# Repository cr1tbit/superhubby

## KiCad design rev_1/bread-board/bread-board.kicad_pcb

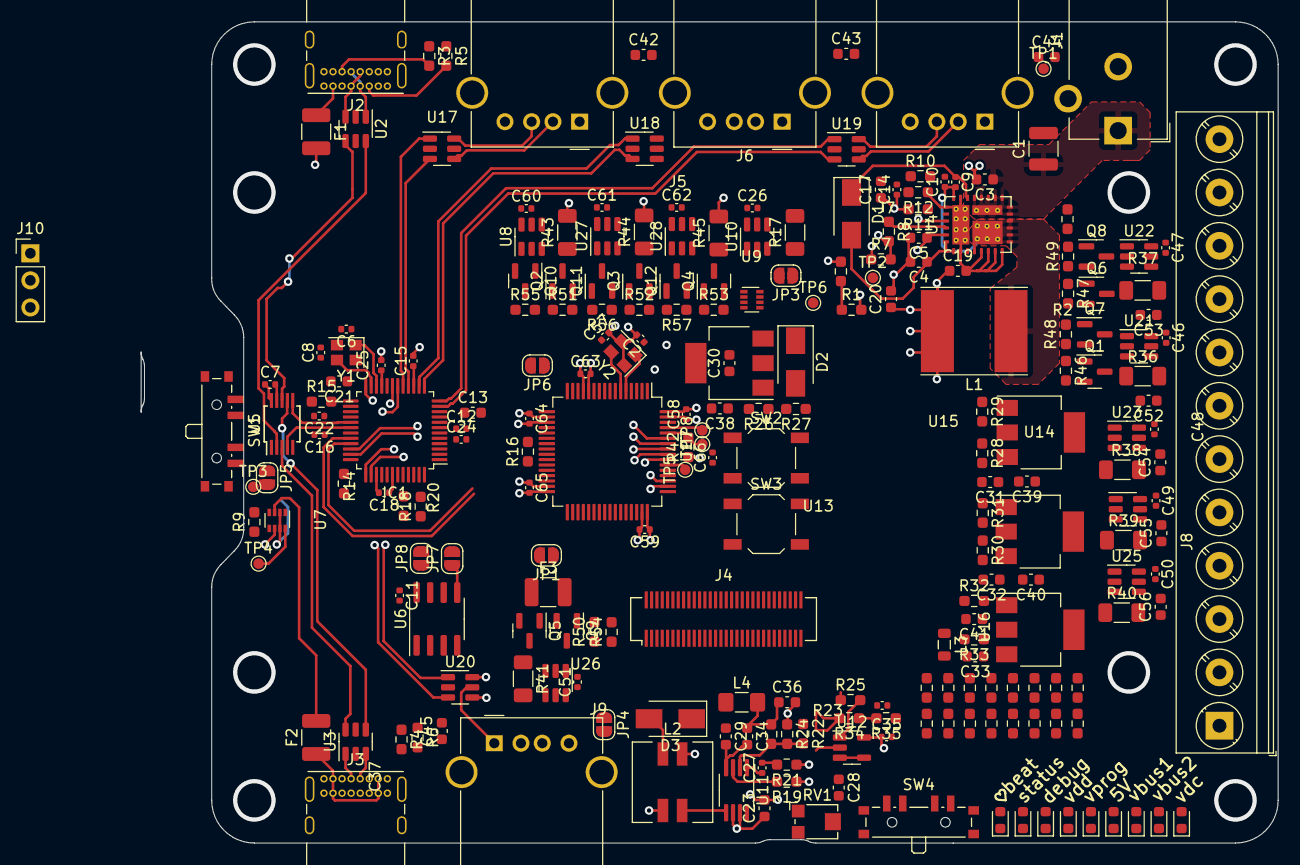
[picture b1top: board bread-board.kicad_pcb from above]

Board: 4 copper layers, 106.6 x 77.0 mm, 232 parts (1 on the bottom side), 174 nets.

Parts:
C1: C; C_1210_3225Metric
C2, C6, C8, C57: 20p; C_0402_1005Metric
C3, C4, C5, C13, C17, C21, C23, C29, C30, C31, C32, C33, C34, C38, C39, C40, C41, C42, C43, C44, C45, C52, C54, C55, C56: 10u; C_0603_1608Metric
C7, C9, C10, C11, C12, C14, C15, C16, C18, C22, C24, C25, C26, C27, C35, C37, C46, C47, C48, C49, C50, C51, C58, C59, C60, C61, C62, C63, C64, C65, C66: 100n; C_0402_1005Metric
C19, C20: 22u; C_0603_1608Metric
C28: 2.2u; C_0603_1608Metric
C36: 47u; C_0603_1608Metric
C53: 10u/16V; C_0603_1608Metric
D1, D2, D3: D_Schottky; D_SMA
D4, D5, D6, D7, D8, D9, D10, D11, D12: LED; LED_0603_1608Metric
F1, F2, F3: 1A; R_1210_3225Metric_Pad1.30x2.65mm_HandSolder
IC1: FE2.1; LQFP-48_7x7mm_P0.5mm
J1: Barrel_Jack_Switch; BarrelJack_CUI_PJ-102AH_Horizontal
J2, J3: USB_C_Receptacle_USB2.0; USB_C_Receptacle_GCT_USB4085
J4: Conn_02x30_Top_Bottom; Hirose_DF12_DF12E3.0-60DP-0.5V_2x30_P0.50mm_Vertical
J5: USB2; USB_A_Molex_67643_Horizontal
J6: USB3; USB_A_Molex_67643_Horizontal
J7: USB4; USB_A_Molex_67643_Horizontal
J8: Screw_Terminal_01x12; TerminalBlock_Phoenix_PT-1,5-12-5.0-H_1x12_P5.00mm_Horizont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
J9: USB1; USB_A_Molex_67643_Horizontal
J10: Conn_01x03; PinHeader_1x03_P2.54mm_Vertical
JP1: FUSE_BYP; SolderJumper-2_P1.3mm_Open_RoundedPad1.0x1.5mm
JP2: USB1_PWR_BYP; SolderJumper-2_P1.3mm_Open_RoundedPad1.0x1.5mm
JP3: 5V_BYP; SolderJumper-2_P1.3mm_Open_RoundedPad1.0x1.5mm
JP4: TEST_POT_ENA; SolderJumper-2_P1.3mm_Open_RoundedPad1.0x1.5mm
JP5: MCU_USB_MUX_ENA; SolderJumper-2_P1.3mm_Open_RoundedPad1.0x1.5mm
JP6, JP7, JP8: X; SolderJumper-2_P1.3mm_Open_RoundedPad1.0x1.5mm
L1: 2.2u; L_Taiyo-Yuden_NR-80xx_HandSoldering
L2: L_Iron_Coupled; L_Wuerth_WE-DD-Typ-M-Typ-S
L3: L_Ferrite; L_0805_2012Metric
L4: L_Iron; L_1206_3216Metric_Pad1.42x1.75mm_HandSolder
Q1, Q2, Q3, Q4, Q5, Q6: AO3401A; SOT-23
Q7, Q8, Q9, Q10, Q11, Q12: BC847; SOT-23
R1: 470k; R_0603_1608Metric_Pad0.98x0.95mm_HandSolder
R2, R7, R8, R9, R10, R11, R12, R14, R15, R16, R19, R20, R21, R26, R27, R28, R29, R30, R31, R32, R33, R34, R35, R72, R73: 100k; R_0603_1608Metric_Pad0.98x0.95mm_HandSolder
R3, R4, R5, R6: 5.1k; R_0603_1608Metric_Pad0.98x0.95mm_HandSolder
R13, R42, R46, R47, R50, R51, R52, R53: 10k; R_0603_1608Metric_Pad0.98x0.95mm_HandSolder
R17: 0.5R; R_1206_3216Metric_Pad1.30x1.75mm_HandSolder
R18: 0R; R_0603_1608Metric_Pad0.98x0.95mm_HandSolder
R22, R24, R58, R60, R61, R62, R63, R64, R65, R66, R67, R68, R69, R70: 2k; R_0603_1608Metric_Pad0.98x0.95mm_HandSolder
R23, R25, R48, R49, R54, R55, R56, R57, R59, R71: 3k; R_0603_1608Metric_Pad0.98x0.95mm_HandSolder
R36, R37, R38, R40: 50mR; R_1206_3216Metric_Pad1.30x1.75mm_HandSolder
R39: 200mR; R_1206_3216Metric_Pad1.30x1.75mm_HandSolder
R41, R43, R44, R45: 100mR; R_1206_3216Metric_Pad1.30x1.75mm_HandSolder
RV1: 10k/DNP; Potentiometer_Bourns_TC33X_Vertical
SW1, SW4: PCM13; SW_SP3T_PCM13
SW2, SW3: BUT_SMD; SW_SPST_TL3342
TP1, TP2: TestPoint; TestPoint_Pad_D1.0mm
TP3: ID1_CTRL; TestPoint_Pad_D1.0mm
TP4: ID1_STATE; TestPoint_Pad_D1.0mm
TP5, TP8: RFUPAD; TestPoint_Pad_D1.0mm
TP6: ID2_STATE; TestPoint_Pad_D1.0mm
TP7: STM_BOOT0; TestPoint_Pad_D1.0mm
U1: STM32F103RFTx; LQFP-64_10x10mm_P0.5mm
U2, U3, U17, U18, U19, U20: USBLC6-2SC6; SOT-23-6
U4: MIC2405x; QFN-28-3EP_5x6mm_MIC2045x
U5: FSUSB30MUX; MSOP-10_3x3mm_P0.5mm
U6: 24LC00; SOIC-8_3.9x4.9mm_P1.27mm
U7, U9: LB66200; SOT-5x3-8
U8, U10, U21, U22, U23, U24, U25, U26, U27, U28: INA181; SOT-23-6
U11: ADP1612; MSOP-8_3x3mm_P0.65mm
U12: MCP6001U; SOT-23-5
U13, U14, U15, U16: AZ1117-ADJ; SOT-223-3_TabPin2
Y1, Y2: 6MHZ 2520; Crystal_SMD_2520-4Pin_2.5x2.0mm

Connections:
+1V8: C40.1, R30.2, R39.1, U15.2 (VO), U24.3 (+)
+3V3: C39.1, R28.2, R38.1, U14.2 (VO), U23.3 (+)
+5V: C12.1, C23.1, C31.1, C32.1, C35.1, D2.2 (A), F3.2, IC1.8 (VDD5), IC1.43 (OVCJ5), IC1.45 (OVCJ1), J4.58, J4.59, J4.60, JP1.1 (A), L2.3, L3.1, Q1.2 (S), Q2.2 (S), Q3.2 (S), Q4.2 (S), R17.2, R20.2, R46.2, R50.2, R51.2, R52.2, R53.2, R67.2, U10.4 (-), U11.6 (VIN), U11.7 (FREQ), U12.5 (V+), U14.3 (VI), U15.3 (VI)
+VDC: C1.1, C3.1, C5.1, J1.1, J8.12, Q6.2 (S), R1.2, R7.2, R8.2, R47.2, R59.2, U4.13 (PVIN), U4.14 (PVIN), U4.15 (PVIN), U4.16 (PVIN), U4.17 (PVIN), U4.18 (PVIN), U4.19 (PVIN), U4.27 (VIN)
+VSW: C34.1, C36.1, L4.2, R23.2, R34.2, R40.1, R69.2, U25.3 (+)
/1V8_OUT: C55.1, J4.9, J4.10, J8.4, R39.2, U24.4 (-)
/1V8_OUT_CURR: U1.10 (PC2), U24.1
/3V3_OUT: C54.1, J4.35, J4.36, J4.37, J8.6, R38.2, U23.4 (-)
/3V3_OUT_CURR: U1.17 (PA3), U23.1
/5V_CURR: U1.14 (PA0), U10.1
/5V_FROM_VDC: C14.1, C17.1, C19.1, C20.1, L1.2, R11.2, SW3.2, U9.6 (VIN2)
/5V_OUT: C52.1, J4.31, J4.32, J4.33, J8.8, R36.2, U21.4 (-)
/5V_OUT_CURR: U1.16 (PA2), U21.1
/ADC_CS: J4.40, U1.33 (PB12)
/ADC_MISO: J4.43, U1.35 (PB14)
/ADC_MOSI: J4.44, U1.36 (PB15)
/ADC_SCK: J4.41, U1.34 (PB13)
/CON_GPIO1: J4.48, R72.1, SW4.1, U1.37 (PC6)
/CON_GPIO2: J4.49, R73.1, SW4.2, U1.38 (PC7)
/CON_GPIO3: J4.50, U1.39 (PC8)
/CON_GPIO4: J4.51, U1.40 (PC9)
/EXT_PS_CONV_EN: J4.11, R8.1, U1.3 (PC14), U4.26 (EN)
/EXT_PS_CONV_PG: J4.12, JP6.1 (A), R7.1, TP2.1, U4.25 (PG)
/EXT_PS_OUT: C53.1, J4.1, J4.2, J4.3, J8.10, R37.2, U22.4 (-)
/EXT_PS_OUT_CURR: U1.15 (PA1), U22.1
/EXT_PS_VLT: R1.1, R2.2, U1.8 (PC0)
/FE21_EEPROM_SCL: JP8.1 (A), U1.53 (PC12), U6.6 (SCL)
/FE21_EEPROM_SDA: JP7.1 (A), U1.52 (PC11), U6.5 (SDA)
/FE21_RST: IC1.40 (XRSTJ), R14.1, U1.41 (PA8)
/FT2232_DM: IC1.37 (DM7), J4.53
/FT2232_DP: IC1.38 (DP7), J4.54
/LOADSW_USB1: R54.1, U1.51 (PC10)
/LOADSW_USB2: R55.1, U1.28 (PB2)
/LOADSW_USB3: R56.1, U1.29 (PB10)
/LOADSW_USB4: R57.1, U1.30 (PB11)
/MCU_DM: IC1.32 (DM5), J4.27
/MCU_DP: IC1.33 (DP5), J4.26
/PS_SCL: J4.46, U1.58 (PB6)
/PS_SDA: J4.47, U1.59 (PB7)
/STM32_DM: IC1.34 (DM6), U1.44 (PA11)
/STM32_DP: IC1.35 (DP6), U1.45 (PA12)
/STM_LED1: R61.2, R63.2, U1.55 (PB3)
/STM_LED2: R65.2, R66.2, U1.56 (PB4)
/STM_LED3: R68.2, R70.2, U1.57 (PB5)
/STM_UART_RX: J4.15, U1.43 (PA10)
/STM_UART_TX: J4.14, U1.42 (PA9)
/SWCLK: J4.21, J10.2, U1.49 (PA14)
/SWDIO: J4.20, J10.1, U1.46 (PA13)
/USB1_CURR: U1.21 (PA5), U26.1
/USB1_DM: IC1.18 (DM1), U20.3 (I/O2)
/USB1_DP: IC1.19 (DP1), U20.1 (I/O1)
/USB2_CURR: U1.22 (PA6), U8.1
/USB2_DM: IC1.16 (DM2), U17.3 (I/O2)
/USB2_DP: IC1.17 (DP2), U17.1 (I/O1)
/USB3_CURR: U1.23 (PA7), U27.1
/USB3_DM: IC1.13 (DM3), U18.3 (I/O2)
/USB3_DP: IC1.14 (DP3), U18.1 (I/O1)
/USB4_CURR: U1.26 (PB0), U28.1
/USB4_DM: IC1.11 (DM4), U19.3 (I/O2)
/USB4_DP: IC1.12 (DP4), U19.1 (I/O1)
/USBIN1_CC1: J2.A5 (CC1), R5.2, U1.25 (PC5)
/USBIN1_CC2: J2.B5 (CC2), R3.2, U1.24 (PC4)
/USBIN2_CC1: J3.A5 (CC1), R6.2, U1.20 (PA4)
/USBIN2_CC2: J3.B5 (CC2), R4.2, U1.27 (PB1)
/USBIN_M: IC1.29 (DMU), U5.6 (D-)
/USBIN_P: IC1.30 (DPU), U5.4 (D+)
/USBIN_SEL: JP5.2 (B), U1.2 (PC13)
/USB_IN_ENA: R9.2, TP3.1, U7.4 (~{ON)
/USB_STATUS_PIN: SW1.2, TP4.1, U7.8 (ST)
/VBUSIN_1: F1.2, JP2.2 (B), R62.2, U7.6 (VIN2)
/VBUSIN_2: F2.2, R64.2, U7.3 (VIN1)
/VBUSIN_COM: JP2.1 (A), JP3.2 (B), U7.2 (VOUT), U7.7 (VOUT), U9.3 (VIN1)
/VDC_SW: C9.2, C10.1, L1.1, U4.4 (SW), U4.9 (SW), U4.10 (SW), U4.11 (SW), U4.12 (SW), U4.22 (CS)
/VPROG_EN: R19.2, U1.62 (PB9), U11.3 (EN)
/VPROG_OUT: C56.1, J4.5, J4.6, J4.7, J8.2, R40.2, U25.4 (-)
/VPROG_OUT_CURR: U1.11 (PC3), U25.1
/VPROG_PWM: J4.13, JP4.1 (A), R25.1, U1.50 (PA15)
/VPROG_VLT: R34.1, R35.2, U1.9 (PC1)
GND: C1.2, C2.2, C3.2, C4.2, C5.2, C6.2, C7.2, C8.2, C11.2, C12.2, C13.2, C15.2, C16.2, C18.2, C19.2, C20.2, C21.2, C22.2, C23.2, C24.2, C25.2, C29.2, C30.2, C31.2, C32.2, C33.2, C34.2, C35.2, C36.2, C37.2, C38.2, C39.2, C40.2, C42.2, C43.2, C44.2, C45.2, C52.2, C53.2, C54.2, C55.2, C56.2, C57.2, C58.1, C59.2, C63.2, C64.1, C65.1, C66.2, D4.1 (K), D5.1 (K), D6.1 (K), D7.1 (K), D8.1 (K), D9.1 (K), D10.1 (K), D11.1 (K), D12.1 (K), IC1.10 (VSS), IC1.24 (VS_PLL), IC1.39 (VSS), J1.2, J2.A1 (GND), J2.A12 (GND), J2.B1 (GND), J2.B12 (GND), J2.S1 (SHIELD), J3.A1 (GND), J3.A12 (GND), J3.B1 (GND), J3.B12 (GND), J3.S1 (SHIELD), J4.4, J4.8, J4.16, J4.22, J4.25, J4.34, J4.38, J4.42, J4.45, J4.52, J4.55, J5.4 (GND), J5.5 (Shield), J6.4 (GND), J6.5 (Shield), J7.4 (GND), J7.5 (Shield), J8.1, J8.3, J8.5, J8.7, J8.9, J8.11, J9.4 (GND), J9.5 (Shield), J10.3, L2.1, Q7.2 (E), Q8.2 (E), Q9.2 (E), Q10.2 (E), Q11.2 (E), Q12.2 (E), R2.1, R3.1, R4.1, R5.1, R6.1, R9.1, R12.1, R15.1, R16.1, R19.1, R21.1, R24.1, R27.1, R29.1, R31.1, R35.1, R42.1, R71.1, RV1.3, SW1.4, SW2.1, U1.12 (VSSA), U1.18 (VSS), U1.31 (VSS), U1.47 (VSS), U1.63 (VSS), U2.2 (-), U3.2 (-), U4.2 (PGND), U4.5 (PGND), U4.6 (PGND), U4.7 (PGND), U4.8 (PGND), U4.21 (PGND), U4.23 (SGND), U5.5 (GND), U5.9 (~{OE), U6.1 (A0), U6.2 (A1), U6.3 (A2), U6.4 (GND), U6.7 (WP), U7.1 (GND), U7.5 (GND), U9.1 (GND), U9.5 (GND), U10.2 (GND), U10.5 (REF), U11.4 (GND), U12.2 (V-), U17.2 (-), U18.2 (-), U19.2 (-), U20.2 (-), Y1.2, Y1.4, Y2.2, Y2.4
GNDA: C26.2, C41.2, C46.2, C47.2, C48.2, C49.2, C50.2, C51.2, C60.2, C61.2, C62.2, R33.1, U8.2 (GND), U8.5 (REF), U21.2 (GND), U21.5 (REF), U22.2 (GND), U22.5 (REF), U23.2 (GND), U23.5 (REF), U24.2 (GND), U24.5 (REF), U25.2 (GND), U25.5 (REF), U26.2 (GND), U26.5 (REF), U27.2 (GND), U27.5 (REF), U28.2 (GND), U28.5 (REF)
unnamed: C2.1, U1.5 (PD0), Y2.1
unnamed: C4.1, D1.2 (A), U4.1 (PVDD), U4.28 (VDD)
unnamed: C6.1, IC1.22 (XIN), Y1.1
unnamed: C8.1, IC1.23 (XOUT), Y1.3
unnamed: C9.1, D1.1 (K), U4.20 (BST)
unnamed: C10.2, R10.2
unnamed: C13.1, C15.1, C16.1, C18.1, IC1.9 (VD33_O), IC1.15 (VD33), IC1.20 (VD33), IC1.26 (VD33), IC1.31 (VD33), IC1.36 (VD33), IC1.42 (VD33)
unnamed: C14.2, C17.2, R10.1, R11.1, R12.2, U4.24 (FB)
unnamed: C21.1, C22.1, C24.1, C25.1, IC1.6 (VD18), IC1.21 (VD_PLL), IC1.25 (VD18_0), IC1.28 (VD18)
unnamed: C27.1, U11.1 (COMP)
unnamed: C27.2, R21.2
unnamed: C28.1, D3.2 (A), L2.2
unnamed: C28.2, L2.4, U11.5 (SW)
unnamed: C29.1, D3.1 (K), L4.1
unnamed: C30.1, D2.1 (K), U13.3 (VI)
unnamed: C33.1, L3.2, U16.3 (VI)
unnamed: C37.1, R25.2, U12.1 (+)
unnamed: C42.1, J5.1 (VBUS), R43.2, U8.4 (-), U17.5 (+)
unnamed: C43.1, J6.1 (VBUS), R44.2, U18.5 (+), U27.4 (-)
unnamed: C44.1, J7.1 (VBUS), R45.2, U19.5 (+), U28.4 (-)
unnamed: C45.1, J9.1 (VBUS), R41.2, U20.5 (+), U26.4 (-)
unnamed: C57.1, U1.6 (PD1), Y2.3
unnamed: C66.1, SW2.2, U1.7 (NRST)
unnamed: D6.2 (A), R62.1
unnamed: D8.2 (A), R64.1
unnamed: D10.2 (A), R67.1
unnamed: D11.2 (A), R69.1
unnamed: F1.1, J2.A4 (VBUS), J2.A9 (VBUS), J2.B4 (VBUS), J2.B9 (VBUS), U2.5 (+)
unnamed: F2.1, J3.A4 (VBUS), J3.A9 (VBUS), J3.B4 (VBUS), J3.B9 (VBUS), U3.5 (+)
unnamed: F3.1, JP1.2 (B), Q5.2 (S)
unnamed: IC1.2 (TESTJ), JP7.2 (B)
unnamed: IC1.3 (LED1), JP8.2 (B)
unnamed: IC1.27 (REXT), R15.2
unnamed: IC1.44 (PWRJ), R18.2
unnamed: J1.3, TP1.1
unnamed: J2.A6 (D+), J2.B6 (D+), U2.1 (I/O1)
unnamed: J2.A7 (D-), J2.B7 (D-), U2.3 (I/O2)
unnamed: J3.A6 (D+), J3.B6 (D+), U3.1 (I/O1)
unnamed: J3.A7 (D-), J3.B7 (D-), U3.3 (I/O2)
unnamed: J5.2 (D-), U17.4 (I/O2)
unnamed: J5.3 (D+), U17.6 (I/O1)
unnamed: J6.2 (D-), U18.4 (I/O2)
unnamed: J6.3 (D+), U18.6 (I/O1)
unnamed: J7.2 (D-), U19.4 (I/O2)
unnamed: J7.3 (D+), U19.6 (I/O1)
unnamed: J9.2 (D-), U20.4 (I/O2)
unnamed: J9.3 (D+), U20.6 (I/O1)
unnamed: JP4.2 (B), RV1.2
unnamed: JP5.1 (A), R13.2, U5.1 (S)
unnamed: Q1.1 (G), Q7.3 (C), R46.1
unnamed: Q1.3 (D), R36.1, U21.3 (+)
unnamed: Q2.3 (D), R43.1, U8.3 (+)
unnamed: Q3.3 (D), R44.1, U27.3 (+)
unnamed: Q4.3 (D), R45.1, U28.3 (+)
unnamed: Q5.1 (G), Q9.3 (C), R50.1
unnamed: Q5.3 (D), R41.1, U26.3 (+)
unnamed: Q6.1 (G), Q8.3 (C), R47.1
unnamed: Q6.3 (D), R37.1, U22.3 (+)
unnamed: Q7.1 (B), R48.2
unnamed: Q8.1 (B), R49.2
unnamed: Q9.1 (B), R54.2
unnamed: Q10.1 (B), R55.2
unnamed: Q2.1 (G), Q10.3 (C), R51.1
unnamed: Q11.1 (B), R56.2
unnamed: Q3.1 (G), Q11.3 (C), R52.1
unnamed: Q12.1 (B), R57.2
unnamed: Q4.1 (G), Q12.3 (C), R53.1
unnamed: R13.1, SW1.3
unnamed: R16.2, SW3.1, U9.4 (~{ON)
unnamed: R18.1, R20.1
unnamed: R22.1, U12.3 (-), U12.4
unnamed: R22.2, R23.1, R24.2, U11.2 (FB)
unnamed: R26.1, R27.2, U13.1 (ADJ)
unnamed: R28.1, R29.2, U14.1 (ADJ)
unnamed: R30.1, R31.2, U15.1 (ADJ)
unnamed: R32.1, R33.2, U16.1 (ADJ)
unnamed: R42.2, TP7.1, U1.60 (BOOT0)
unnamed: D5.2 (A), R58.1, R60.1
unnamed: D4.2 (A), R59.1
unnamed: D7.2 (A), R61.1, R63.1
unnamed: D9.2 (A), R65.1, R66.1
unnamed: D12.2 (A), R68.1, R70.1
unnamed: R71.2, SW4.3
unnamed: TP6.1, U9.8 (ST)
unnamed: JP6.2 (B), U1.4 (PC15)
unnamed: TP5.1, U1.54 (PD2)
unnamed: TP8.1, U1.61 (PB8)
unnamed: U2.4 (I/O2), U5.8 (HSD1-)
unnamed: U2.6 (I/O1), U5.2 (HSD1+)
unnamed: U3.4 (I/O2), U5.7 (HSD2-)
unnamed: U3.6 (I/O1), U5.3 (HSD2+)
VBUS: IC1.41 (VBUSM), JP3.1 (A), R17.1, U9.2 (VOUT), U9.7 (VOUT), U10.3 (+)
VDD: C7.1, C11.1, C38.1, C58.2, C59.1, C64.2, C65.2, J4.28, J4.29, J4.30, R14.2, R26.2, R58.2, R60.2, R72.2, R73.2, RV1.1, SW1.1, U1.1 (VBAT), U1.19 (VDD), U1.32 (VDD), U1.48 (VDD), U1.64 (VDD), U5.10 (VCC), U6.8 (VCC), U13.2 (VO)
VDDA: C26.1, C41.1, C46.1, C47.1, C48.1, C49.1, C50.1, C51.1, C60.1, C61.1, C62.1, C63.1, R32.2, U1.13 (VDDA), U8.6 (V+), U10.6 (V+), U16.2 (VO), U21.6 (V+), U22.6 (V+), U23.6 (V+), U24.6 (V+), U25.6 (V+), U26.6 (V+), U27.6 (V+), U28.6 (V+)

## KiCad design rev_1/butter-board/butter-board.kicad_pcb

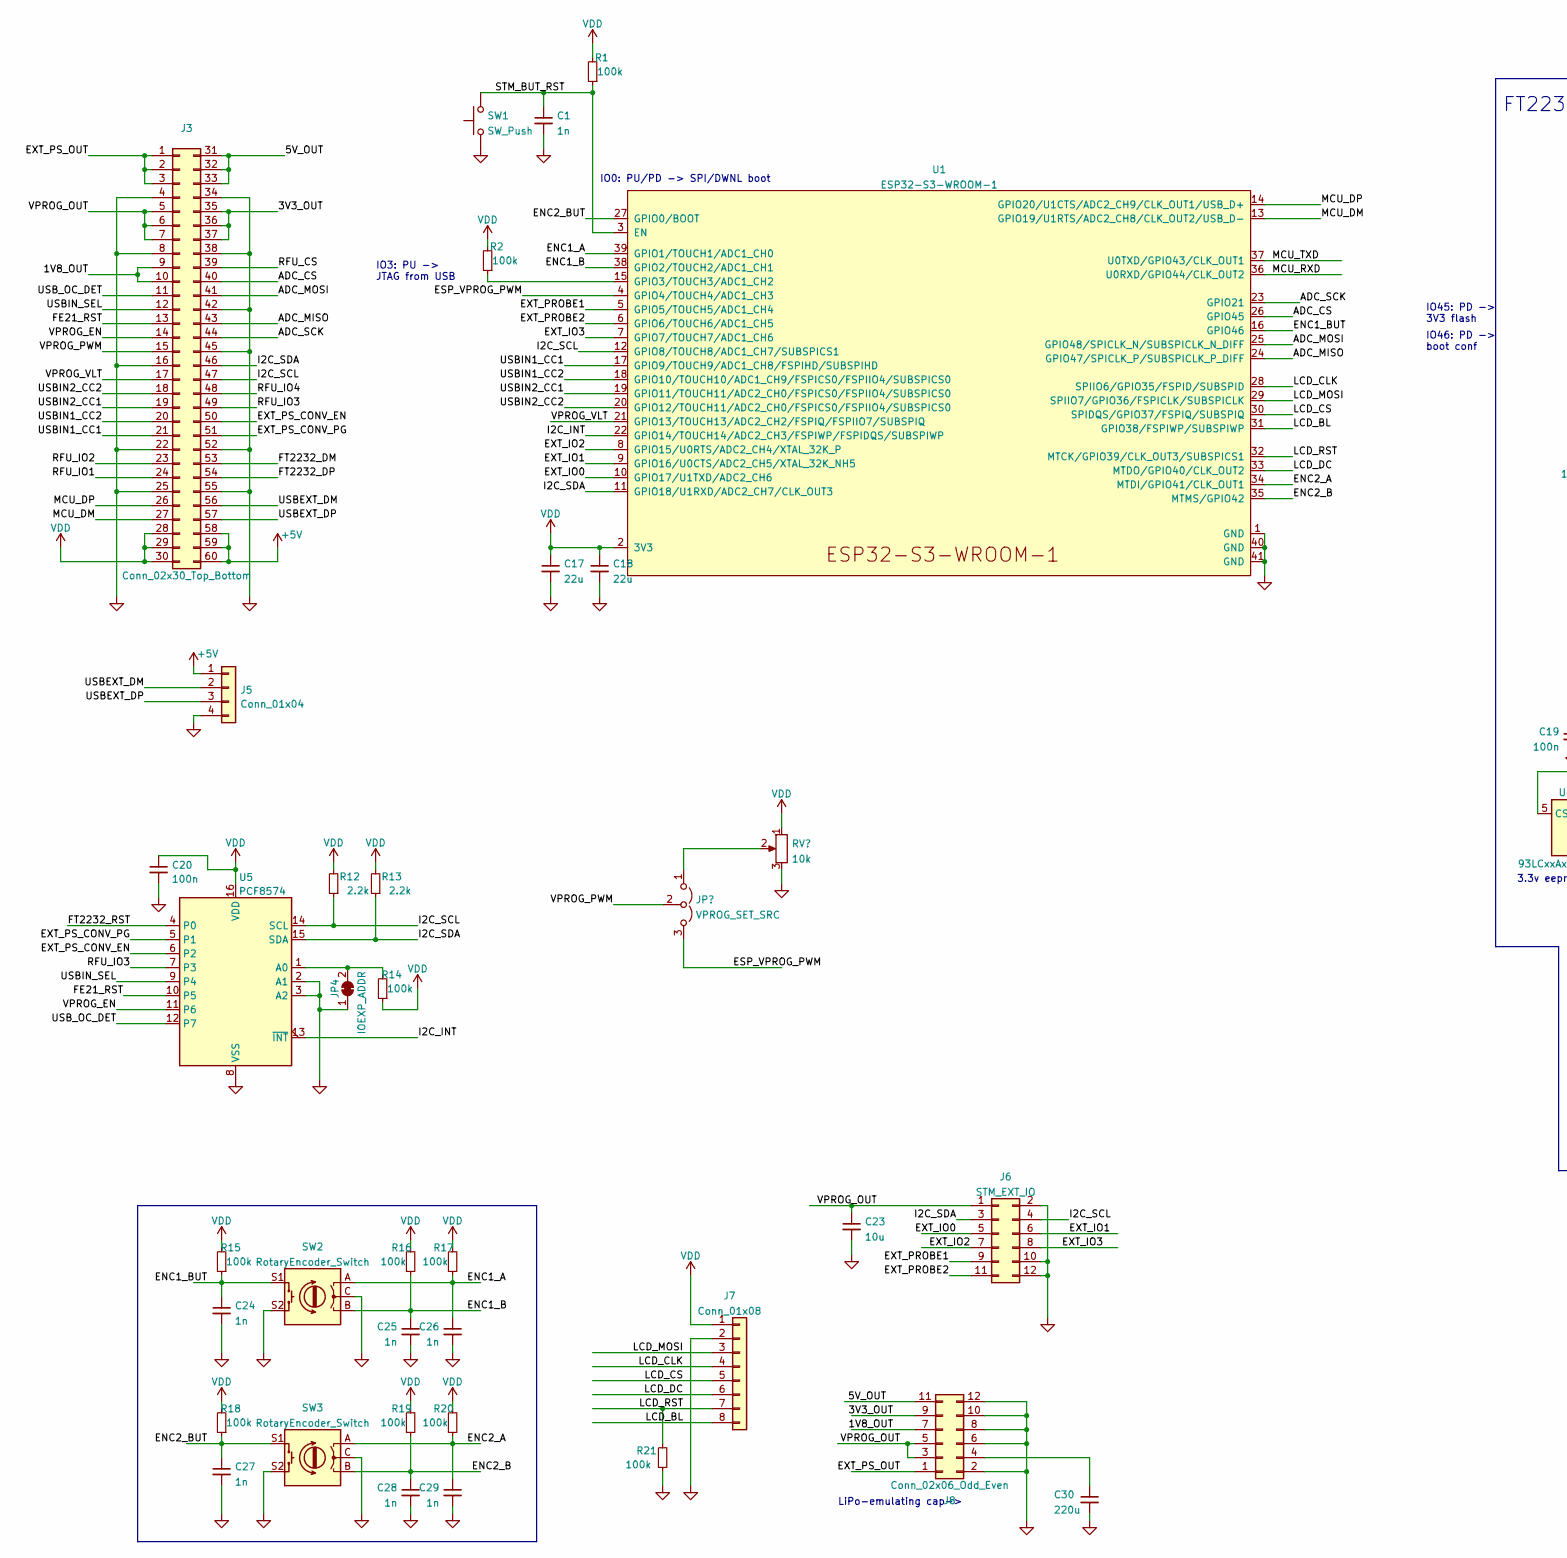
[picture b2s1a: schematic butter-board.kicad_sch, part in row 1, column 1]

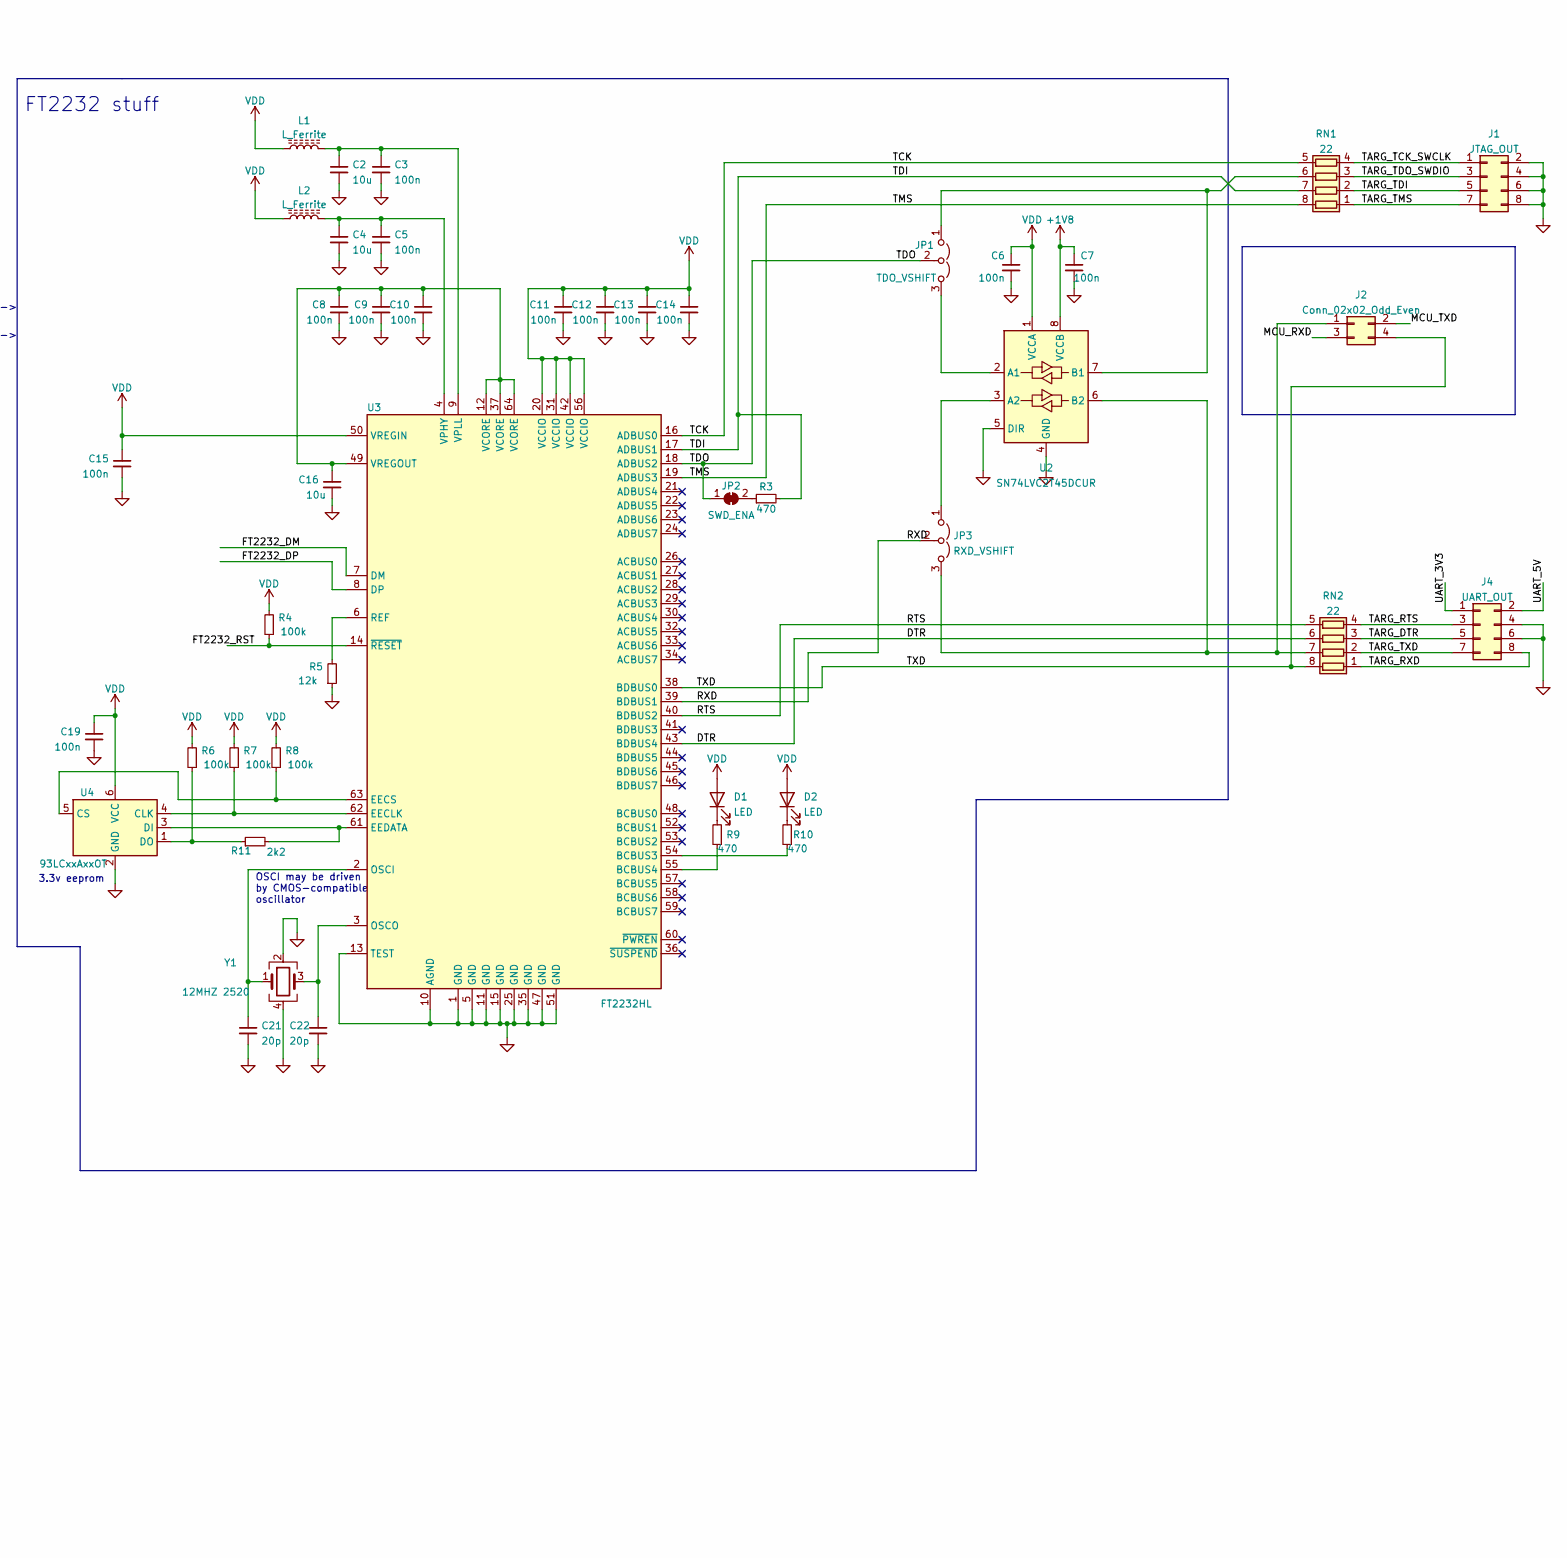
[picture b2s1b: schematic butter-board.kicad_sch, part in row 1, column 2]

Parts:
C1, C24, C25, C26, C27, C28, C29: 1n; C_0402_1005Metric
C2, C4, C16, C23: 10u; C_0805_2012Metric
C3, C5, C6, C7, C8, C9, C10, C11, C12, C13, C14, C15, C19, C20: 100n; C_0402_1005Metric
C17, C18: 22u; C_0805_2012Metric
C21, C22: 20p; C_0402_1005Metric
C30: 220u; CP_Radial_D5.0mm_P2.50mm
D1, D2: LED; LED_0805_2012Metric_Pad1.15x1.40mm_HandSolder
J1: JTAG_OUT; PinHeader_2x04_P2.54mm_Horizontal
J2: Conn_02x02_Odd_Even; PinHeader_2x02_P2.54mm_Vertical
J3: Conn_02x30_Top_Bottom; Hirose_DF12_DF12C3.0-60DS-0.5V_2x30_P0.50mm_Vertical
J4: UART_OUT; PinHeader_2x04_P2.54mm_Horizontal
J5: Conn_01x04; PinHeader_1x04_P2.54mm_Vertical
J6: STM_EXT_IO; PinHeader_2x06_P2.54mm_Horizontal
J7: Conn_01x08; PinSocket_1x08_P2.54mm_Vertical
J8: Conn_02x06_Odd_Even; PinHeader_2x06_P2.54mm_Horizontal
JP1: TDO_VSHIFT; PinHeader_1x03_P2.54mm_Vertical
JP2: SWD_ENA; SolderJumper-2_P1.3mm_Bridged2Bar_RoundedPad1.0x1.5mm
JP3: RXD_VSHIFT; PinHeader_1x03_P2.54mm_Vertical
JP4: IOEXP_ADDR; SolderJumper-2_P1.3mm_Bridged2Bar_RoundedPad1.0x1.5mm
L1, L2: L_Ferrite; L_0805_2012Metric
R1, R2, R4, R6, R7, R8, R14, R15, R16, R17, R18, R19, R20, R21: 100k; R_0402_1005Metric
R3, R9, R10: 470; R_0402_1005Metric
R5: 12k; R_0402_1005Metric
R11: 2k2; R_0402_1005Metric
R12, R13: 2.2k; R_0402_1005Metric
RN1, RN2: 22; R_Array_Convex_4x0603
SW1: SW_Push; SW_SPST_B3U-3000P-B
SW2, SW3: RotaryEncoder_Switch; RotaryEncoder_Alps_EC12E-Switch_Vertical_H20mm_CircularMoun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
U1: ESP32-S3-WROOM-1
U2: SN74LVC2T45DCUR; VSSOP-8_2.4x2.1mm_P0.5mm
U3: FT2232HL; LQFP-64_10x10mm_P0.5mm
U4: 93LCxxAxxOT; SOT-23-6
U5: PCF8574; SOIC-16W_7.5x10.3mm_P1.27mm
Y1: 12MHZ 2520; Crystal_SMD_2520-4Pin_2.5x2.0mm

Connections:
+1V8: C7.1, U2.8 (VCCB)
+5V: J3.58, J3.59, J3.60, J5.1
/1V8_OUT: J3.9, J3.10, J8.7
/3V3_OUT: J3.35, J3.36, J3.37, J8.9
/5V_OUT: J3.31, J3.32, J3.33, J8.11
/ADC_CS: J3.40, U1.26 (GPIO45)
/ADC_MISO: J3.43, U1.24 (GPIO47/SPICLK_P/SUBSPICLK_P_DIFF)
/ADC_MOSI: J3.41, U1.25 (GPIO48/SPICLK_N/SUBSPICLK_N_DIFF)
/ADC_SCK: J3.44, U1.23 (GPIO21)
/DTR: RN2.6 (R3.2), U3.43 (BDBUS4)
/ENC1_A: C26.1, R17.1, SW2.A, U1.39 (GPIO1/TOUCH1/ADC1_CH0)
/ENC1_B: C25.1, R16.1, SW2.B, U1.38 (GPIO2/TOUCH2/ADC1_CH1)
/ENC1_BUT: C24.1, R15.1, SW2.S1, U1.16 (GPIO46)
/ENC2_A: C29.1, R20.1, SW3.A, U1.34 (MTDI/GPIO41/CLK_OUT1)
/ENC2_B: C28.1, R19.1, SW3.B, U1.35 (MTMS/GPIO42)
/ENC2_BUT: C27.1, R18.1, SW3.S1, U1.27 (GPIO0/BOOT)
/EXT_IO0: J6.5, U1.10 (GPIO17/U1TXD/ADC2_CH6)
/EXT_IO1: J6.6, U1.9 (GPIO16/U0CTS/ADC2_CH5/XTAL_32K_NH5)
/EXT_IO2: J6.7, U1.8 (GPIO15/U0RTS/ADC2_CH4/XTAL_32K_P)
/EXT_IO3: J6.8, U1.7 (GPIO7/TOUCH7/ADC1_CH6)
/EXT_PROBE1: J6.9, U1.5 (GPIO5/TOUCH5/ADC1_CH4)
/EXT_PROBE2: J6.11, U1.6 (GPIO6/TOUCH6/ADC1_CH5)
/EXT_PS_CONV_EN: J3.50, U5.6 (P2)
/EXT_PS_CONV_PG: J3.51, U5.5 (P1)
/EXT_PS_OUT: J3.1, J3.2, J3.3, J8.1
/FE21_RST: J3.13, U5.10 (P5)
/FT2232_DM: J3.53, U3.7 (DM)
/FT2232_DP: J3.54, U3.8 (DP)
/FT2232_RST: R4.1, U3.14 (~RESET), U5.4 (P0)
/I2C_INT: U1.22 (GPIO14/TOUCH14/ADC2_CH3/FSPIWP/FSPIDQS/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), U5.13 (~INT)
/I2C_SCL: J3.47, J6.4, R12.1, U1.12 (GPIO8/TOUCH8/ADC1_CH7/SUBSPICS1), U5.14 (SCL)
/I2C_SDA: J3.46, J6.3, R13.1, U1.11 (GPIO18/U1RXD/ADC2_CH7/CLK_OUT3), U5.15 (SDA)
/LCD_BL: J7.8, U1.31 (GPIO38/FSPIWP/SUBSPIWP)
/LCD_CLK: J7.4, U1.28 (SPIIO6/GPIO35/FSPID/SUBSPID)
/LCD_CS: J7.5, U1.30 (SPIDQS/GPIO37/FSPIQ/SUBSPIQ)
/LCD_DC: J7.6, U1.33 (MTDO/GPIO40/CLK_OUT2)
/LCD_MOSI: J7.3, U1.29 (SPIIO7/GPIO36/FSPICLK/SUBSPICLK)
/LCD_RST: J7.7, R21.2, U1.32 (MTCK/GPIO39/CLK_OUT3/SUBSPICS1)
/MCU_DM: J3.27, U1.13 (GPIO19/U1RTS/ADC2_CH8/CLK_OUT2/USB_D-)
/MCU_DP: J3.26, U1.14 (GPIO20/U1CTS/ADC2_CH9/CLK_OUT1/USB_D+)
/MCU_RXD: J2.3, U1.36 (U0RXD/GPIO44/CLK_OUT2)
/MCU_TXD: J2.2, U1.37 (U0TXD/GPIO43/CLK_OUT1)
/RFU_CS: J3.39
/RFU_IO1: J3.24
/RFU_IO2: J3.23
/RFU_IO3: J3.49, U5.7 (P3)
/RFU_IO4: J3.48
/RTS: RN2.5 (R4.2), U3.40 (BDBUS2)
/RXD: JP3.2 (C), U3.39 (BDBUS1)
/STM_BUT_RST: C1.1, R1.1, SW1.2, U1.3 (EN)
/TARG_DTR: J4.5, RN2.3 (R3.1)
/TARG_RTS: J4.3, RN2.4 (R4.1)
/TARG_RXD: J4.8, RN2.1 (R1.1)
/TARG_TCK_SWCLK: J1.1, RN1.4 (R4.1)
/TARG_TDI: J1.5, RN1.2 (R2.1)
/TARG_TDO_SWDIO: J1.3, RN1.3 (R3.1)
/TARG_TMS: J1.7, RN1.1 (R1.1)
/TARG_TXD: J4.7, RN2.2 (R2.1)
/TCK: RN1.5 (R4.2), U3.16 (ADBUS0)
/TDI: R3.2, RN1.7 (R2.2), U3.17 (ADBUS1)
/TDO: JP1.2 (C), JP2.1 (A), U3.18 (ADBUS2)
/TMS: RN1.8 (R1.2), U3.19 (ADBUS3)
/TXD: J2.4, RN2.8 (R1.2), U3.38 (BDBUS0)
/UART_3V3: J4.1
/UART_5V: J4.2
/USBEXT_DM: J3.56, J5.2
/USBEXT_DP: J3.57, J5.3
/USBIN1_CC1: J3.21, U1.17 (GPIO9/TOUCH9/ADC1_CH8/FSPIHD/SUBSPIHD)
/USBIN1_CC2: J3.20, U1.18 (GPIO10/TOUCH10/ADC1_CH9/FSPICS0/FSPIIO4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)
/USBIN2_CC1: J3.19, U1.19 (GPIO11/TOUCH11/ADC2_CH0/FSPICS0/FSPIIO4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)
/USBIN2_CC2: J3.18, U1.20 (GPIO12/TOUCH11/ADC2_CH0/FSPICS0/FSPIIO4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)
/USBIN_SEL: J3.12, U5.9 (P4)
/USB_OC_DET: J3.11, U5.12 (P7)
/VPROG_EN: J3.14, U5.11 (P6)
/VPROG_OUT: C23.1, J3.5, J3.6, J3.7, J6.1, J8.3, J8.5
/VPROG_VLT: J3.17, U1.21 (GPIO13/TOUCH13/ADC2_CH2/FSPIQ/FSPIIO7/S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)
GND: C1.2, C2.2, C3.2, C4.2, C5.2, C6.2, C7.2, C8.2, C9.2, C10.2, C11.2, C12.2, C13.2, C14.2, C15.2, C16.2, C17.2, C18.2, C19.2, C20.2, C21.2, C22.2, C23.2, C24.2, C25.2, C26.2, C27.2, C28.2, C29.2, C30.2, J1.2, J1.4, J1.6, J1.8, J3.4, J3.8, J3.16, J3.22, J3.25, J3.34, J3.38, J3.42, J3.45, J3.52, J3.55, J4.4, J4.6, J5.4, J6.2, J6.10, J6.12, J7.2, J8.2, J8.6, J8.8, J8.10, J8.12, JP4.1 (A), R5.1, R21.1, SW1.1, SW2.C, SW2.S2, SW3.C, SW3.S2, U1.1 (GND), U1.40 (GND), U1.41 (GND), U2.4 (GND), U2.5 (DIR), U3.1 (GND), U3.5 (GND), U3.10 (AGND), U3.11 (GND), U3.13 (TEST), U3.15 (GND), U3.25 (GND), U3.35 (GND), U3.47 (GND), U3.51 (GND), U4.2 (GND), U5.2 (A1), U5.3 (A2), U5.8 (VSS), Y1.2, Y1.4
unnamed: C2.1, C3.1, L1.2, U3.9 (VPLL)
unnamed: C4.1, C5.1, L2.2, U3.4 (VPHY)
unnamed: C8.1, C9.1, C10.1, C16.1, U3.12 (VCORE), U3.37 (VCORE), U3.49 (VREGOUT), U3.64 (VCORE)
unnamed: C21.1, U3.2 (OSCI), Y1.1
unnamed: C22.1, U3.3 (OSCO), Y1.3
unnamed: C30.1, J8.4
unnamed: D1.1 (K), R9.2
unnamed: D2.1 (K), R10.2
unnamed: J2.1, JP3.3 (B), RN2.7 (R2.2), U2.6 (B2)
unnamed: JP1.1 (A), RN1.6 (R3.2), U2.7 (B1)
unnamed: JP1.3 (B), U2.2 (A1)
unnamed: JP2.2 (B), R3.1
unnamed: JP3.1 (A), U2.3 (A2)
unnamed: JP4.2 (B), R14.2, U5.1 (A0)
unnamed: R2.1, U1.15 (GPIO3/TOUCH3/ADC1_CH2)
unnamed: R5.2, U3.6 (REF)
unnamed: R7.1, U3.62 (EECLK), U4.4 (CLK)
unnamed: R8.1, U3.63 (EECS), U4.5 (CS)
unnamed: R9.1, U3.55 (BCBUS4)
unnamed: R10.1, U3.54 (BCBUS3)
unnamed: R6.1, R11.1, U4.1 (DO)
unnamed: R11.2, U3.61 (EEDATA), U4.3 (DI)
VDD: C6.1, C11.1, C12.1, C13.1, C14.1, C15.1, C17.1, C18.1, C19.1, C20.1, D1.2 (A), D2.2 (A), J3.28, J3.29, J3.30, J7.1, L1.1, L2.1, R1.2, R2.2, R4.2, R6.2, R7.2, R8.2, R12.2, R13.2, R14.1, R15.2, R16.2, R17.2, R18.2, R19.2, R20.2, U1.2 (3V3), U2.1 (VCCA), U3.20 (VCCIO), U3.31 (VCCIO), U3.42 (VCCIO), U3.50 (VREGIN), U3.56 (VCCIO), U4.6 (VCC), U5.16 (VDD)

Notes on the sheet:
IO0: PU/PD -> SPI/DWNL boot
IO45: PD -> 3V3 flash
IO3: PU -> JTAG from USB
IO46: PD -> boot conf
3.3v eeprom
LiPo-emulating cap->
FT2232 stuff
OSCI may be driven by CMOS-compatible oscillator

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
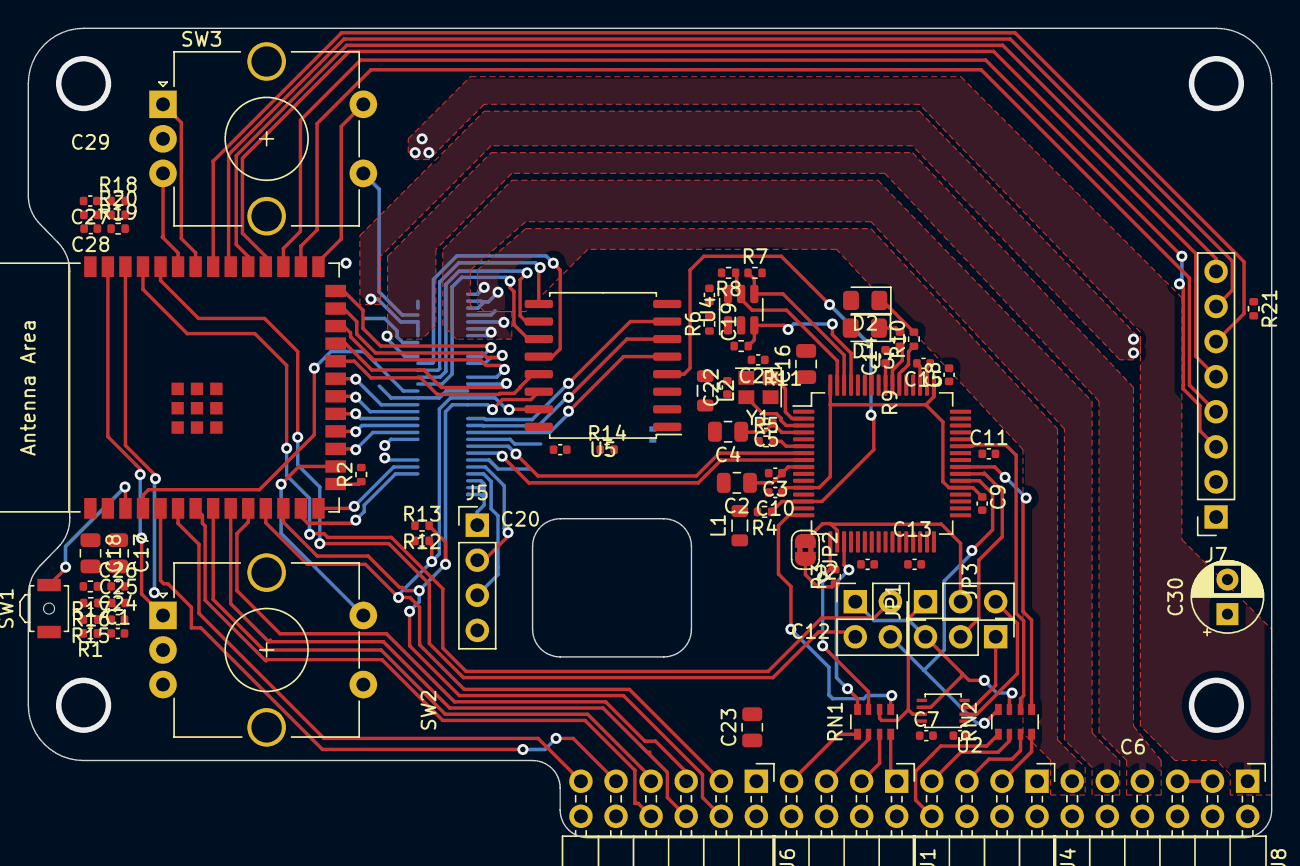
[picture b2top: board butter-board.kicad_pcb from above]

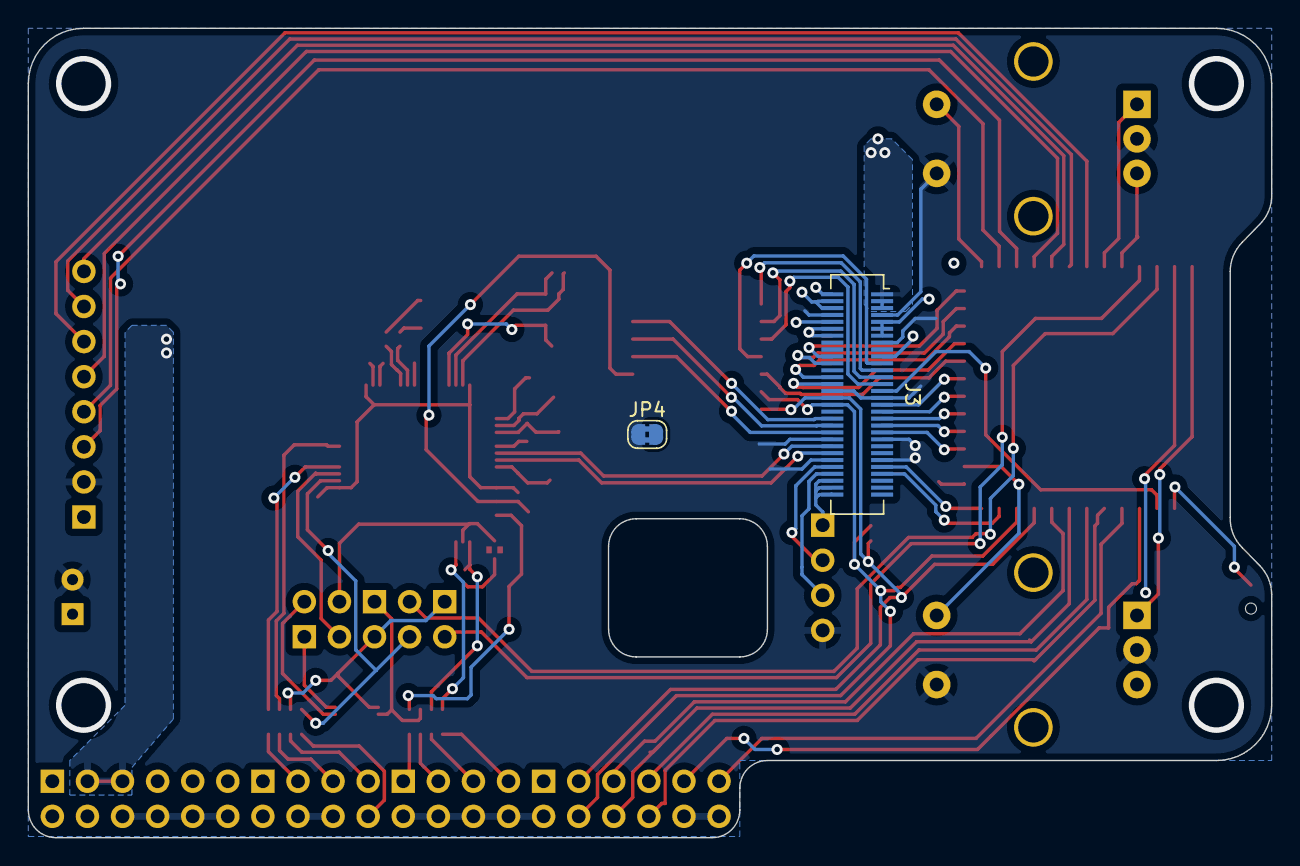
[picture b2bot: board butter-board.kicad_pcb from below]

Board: 4 copper layers, 90.0 x 58.6 mm, 78 parts (2 on the bottom side), 95 nets.
